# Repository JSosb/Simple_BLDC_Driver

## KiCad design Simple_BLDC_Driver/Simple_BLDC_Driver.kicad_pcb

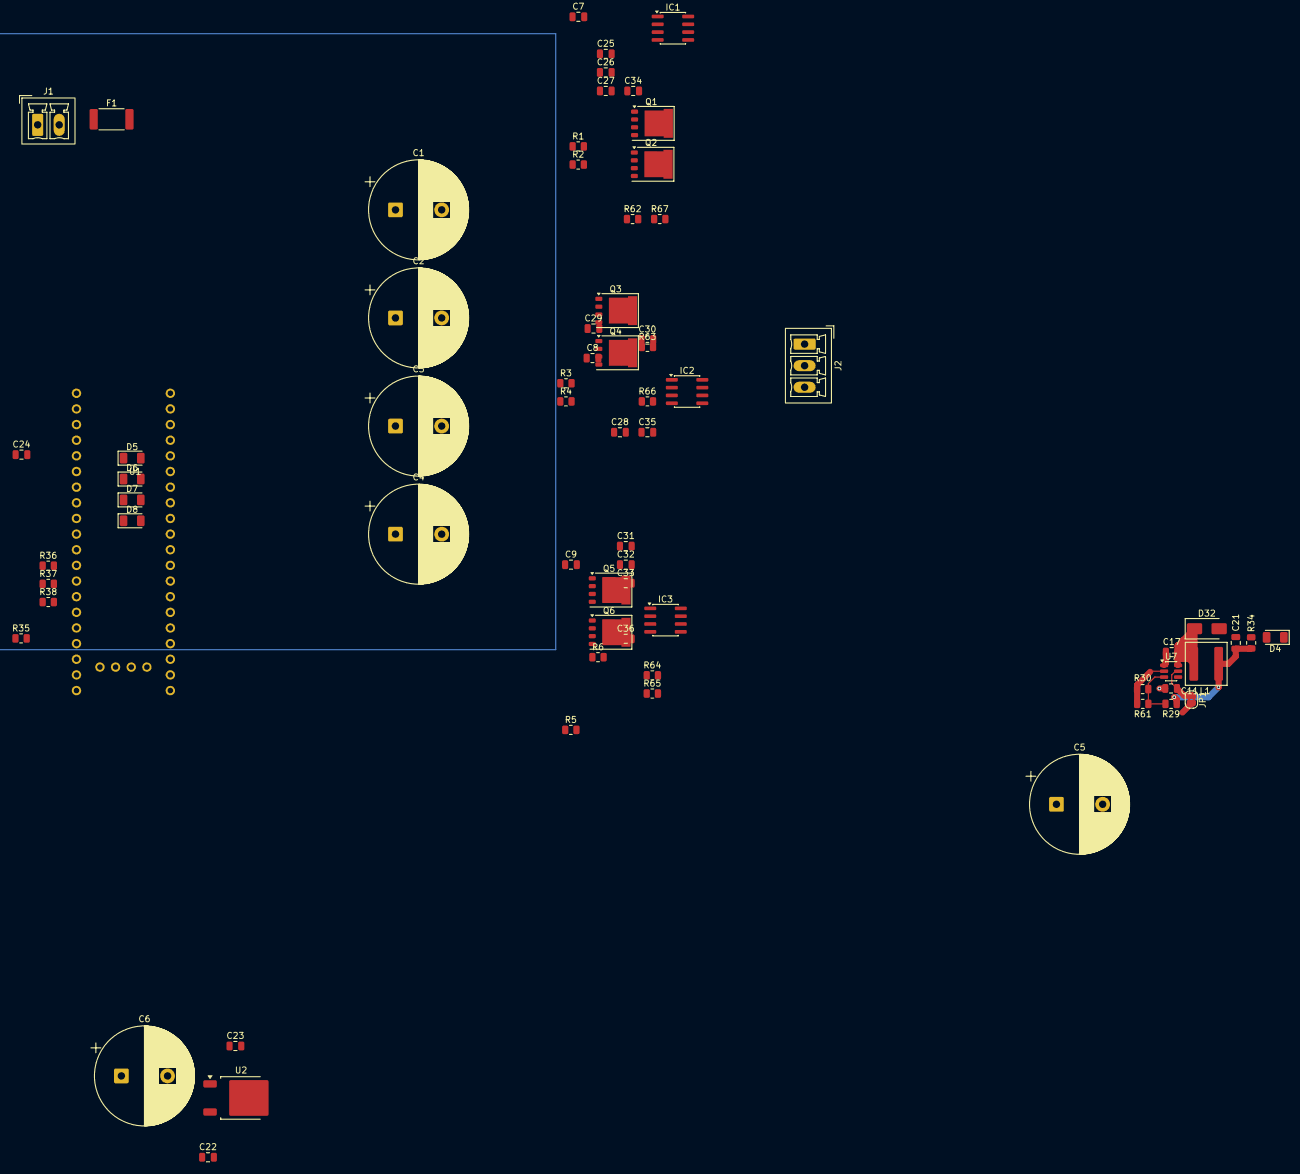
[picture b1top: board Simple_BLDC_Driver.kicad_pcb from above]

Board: 2 copper layers, 70 parts (0 on the bottom side), 36 nets.

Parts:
C1, C2, C3, C4, C5, C6: C_Polarized; CP_Radial_D16.0mm_P7.50mm
C7, C8, C9, C17: 100n; C_0805_2012Metric
C11, C21, C22, C24, C25, C26, C27, C28, C29, C30, C31, C32, C33: 10u; C_0805_2012Metric
C23: 1u; C_0805_2012Metric
C34, C35, C36: 10n; C_0805_2012Metric
D4, D5, D6, D7, D8: YLED1206R; LED_1206_3216Metric
D32: D_Schottky; D_SMA
F1: Fuse; Fuse_2512_6332Metric
IC1, IC2, IC3: UCC27282DR; SOIC-8_3.9x4.9mm_P1.27mm
J1: Conn_01x02; PhoenixContact_MCV_1,5_2-G-3.5_1x02_P3.50mm_Vertical
J2: Conn_01x03; PhoenixContact_MCV_1,5_3-G-3.5_1x03_P3.50mm_Vertical
JP1: SolderJumper_2_Bridged; SolderJumper-2_P1.3mm_Bridged2Bar_RoundedPad1.0x1.5mm
L1: 12uH; L_Coilcraft_XAL6020-XXX
Q1, Q2, Q3, Q4, Q5, Q6: Q_NMOS; PQFN-8-EP_6x5mm_P1.27mm_Generic
R1, R2, R3, R4, R5, R6: 10R; R_0805_2012Metric
R29, R30, R61: R; R_0805_2012Metric
R34: 2K; R_0805_2012Metric
R35, R36, R37, R38: 220R; R_0805_2012Metric
R62, R63, R64, R65, R66, R67: 10k; R_0805_2012Metric
U1: BP; blue_pill
U2: L7805; TO-252-2
U7: LV2842XLVDDCR; SOT-23-6

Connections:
+5V: C6.1, C22.1, C24.1, U1.5V, U2.3 (OUT)
+12V: C5.1, C21.1, C23.1, C25.1, C28.1, C31.1, IC1.1 (VDD), IC2.1 (VDD), IC3.1 (VDD), L1.2, R29.1, R34.1, U2.1 (IN)
+24V: C1.1, C2.1, C3.1, C4.1, C26.1, C27.1, C29.1, C30.1, C32.1, C33.1, F1.2, JP1.2 (B)
/H_A: IC1.5 (HI), R67.1, U1.PA8
/H_B: IC2.5 (HI), R66.1, U1.PA9
/H_C: IC3.5 (HI), R65.1, U1.PA10
/L_A: IC1.6 (LI), R62.1, U1.PB13
/L_B: IC2.6 (LI), R63.1, U1.PB14
/L_C: IC3.6 (LI), R64.1, U1.PB15
GND: C1.2, C2.2, C3.2, C4.2, C5.2, C6.2, C11.2, C21.2, C22.2, C23.2, C24.2, C25.2, C26.2, C27.2, C28.2, C29.2, C30.2, C31.2, C32.2, C33.2, C34.2, C35.2, C36.2, D4.1 (K), D5.1 (K), D6.1 (K), D7.1 (K), D8.1 (K), D32.2 (A), IC1.7 (VSS), IC2.7 (VSS), IC3.7 (VSS), J1.1, R30.2, R61.2, R62.2, R63.2, R64.2, R65.2, R66.2, R67.2, U1.G (GND), U2.2 (GND), U7.2 (GND)
unnamed: D4.2 (A), R34.2
unnamed: D5.2 (A), R38.2
unnamed: D6.2 (A), R37.2
unnamed: D7.2 (A), R36.2
unnamed: D8.2 (A), R35.2
unnamed: C17.2, D32.1 (K), L1.1, U7.6 (SW)
unnamed: C7.1, IC1.2 (HB)
unnamed: IC1.3 (HO), R1.1
unnamed: C7.2, C34.1, IC1.4 (HS), J2.1
unnamed: IC1.8 (LO), R2.1
unnamed: C8.1, IC2.2 (HB)
unnamed: IC2.3 (HO), R3.1
unnamed: C8.2, C35.1, IC2.4 (HS), J2.2
unnamed: IC2.8 (LO), R4.1
unnamed: C9.1, IC3.2 (HB)
unnamed: IC3.3 (HO), R5.1
unnamed: C9.2, C36.1, IC3.4 (HS), J2.3
unnamed: IC3.8 (LO), R6.1
unnamed: F1.1, J1.2
unnamed: C11.1, JP1.1 (A), U7.5 (VIN)
unnamed: R35.1, U1.PB11
unnamed: R36.1, U1.PB10
unnamed: R37.1, U1.PB1
unnamed: R38.1, U1.PB0
unnamed: C17.1, U7.1 (CB)
unnamed: R29.2, R30.1, R61.1, U7.3 (FB)

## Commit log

2026-06-11 init project
2026-06-13 start the shematic
